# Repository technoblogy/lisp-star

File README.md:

# Lisp Star
A star-shaped pendant that you can program in Lisp.

For more information see: <http://www.technoblogy.com/show?2AMW>.

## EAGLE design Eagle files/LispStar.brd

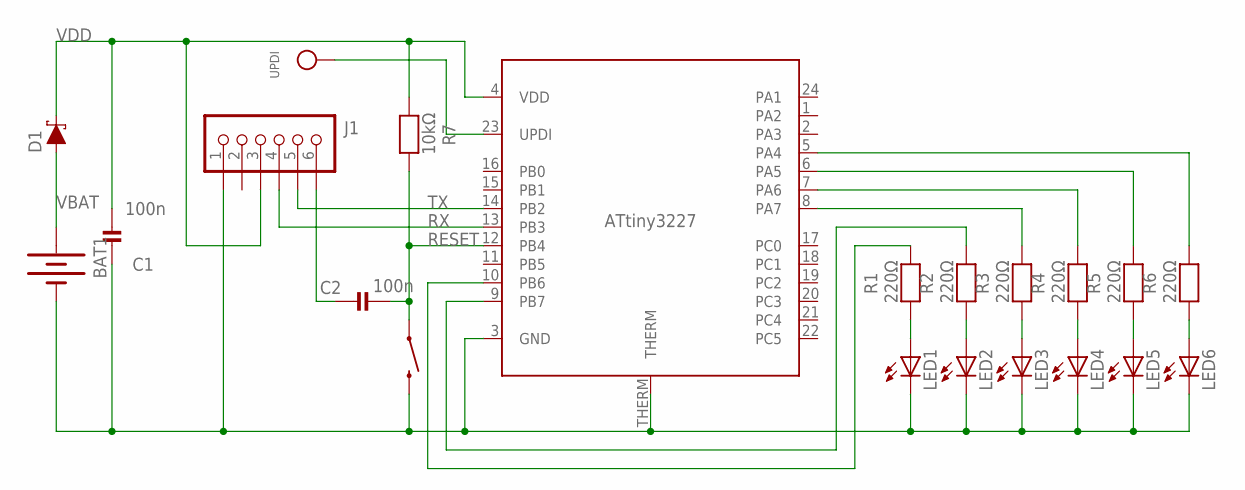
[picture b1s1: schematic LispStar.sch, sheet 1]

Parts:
BAT1: BATTERY12MM; BATTCON_12MM
C1, C2: 100n; _0805MP
D1: 3A/10V/280mV; SOD-323
J1: AVR_SPI_PRG_6LINETESTPOINTS; 2X3_TEST_POINTS
LED1, LED2, LED3, LED4, LED5, LED6: LEDCHIPLED_0805; CHIPLED_0805
R1, R2, R3, R4, R5, R6: 220Ω; _0805MP
R7: 10kΩ; _0805MP
S2: SWITCH-MOMENTARY-2SMD; TACTILE-SWITCH-SMD
U1: ATtiny3227; QFN24_4MM
UPDI: TESTPOINTROUND1MM; TESTPOINT_ROUND_1MM

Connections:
GND: BAT1.GND (-), C1.2, J1.1, LED1.C, LED2.C, LED3.C, LED4.C, LED5.C, LED6.C, S2.3 (2), U1.3 (GND), U1.THERM
unnamed: U1.23 (UPDI), UPDI.P$1
unnamed: LED2.A, R2.1
unnamed: LED1.A, R1.1
unnamed: LED3.A, R3.1
unnamed: C2.1, J1.6
unnamed: LED4.A, R4.1
unnamed: LED5.A, R5.1
unnamed: LED6.A, R6.1
unnamed: R6.2, U1.5 (PA4)
unnamed: R5.2, U1.6 (PA5)
unnamed: R4.2, U1.7 (PA6)
unnamed: R3.2, U1.8 (PA7)
unnamed: R2.2, U1.9 (PB7)
unnamed: R1.2, U1.10 (PB6)
RESET: C2.2, R7.1, S2.1, U1.12 (PB4)
RX: J1.4, U1.13 (PB3)
TX: J1.5, U1.14 (PB2)
VBAT: BAT1.PWR@1 (+), D1.A
VDD: C1.1, D1.C, J1.3, R7.2, U1.4 (VDD)

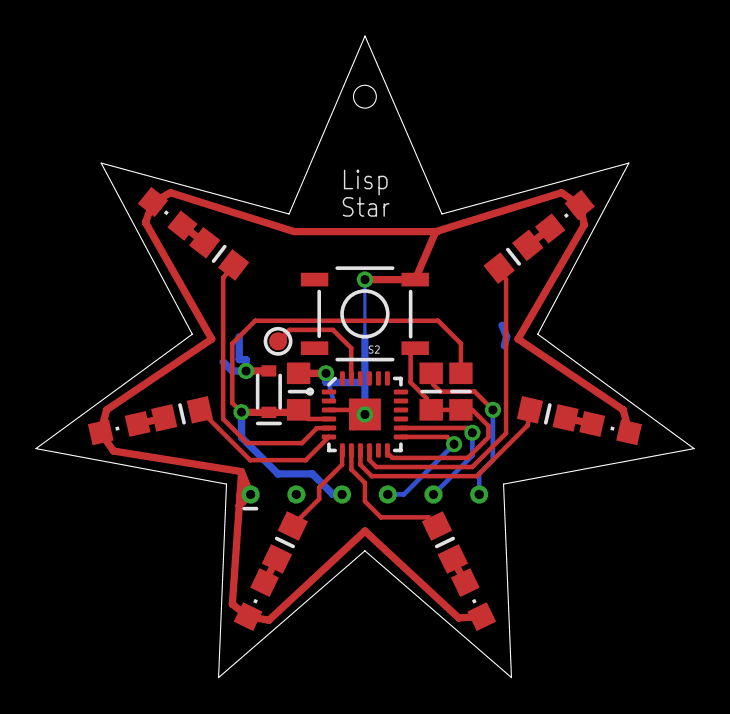
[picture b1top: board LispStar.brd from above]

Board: 2 copper layers, 36.6 x 35.6 mm, 21 parts (1 on the bottom side), 20 nets.

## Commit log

2022-12-08 Version 1 - 8th December 2022

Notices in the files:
parts and their libraries:
SparkFun-Electromechanical: Licensing: Creative Commons ShareAlike 4.0 International - https://creativecommons.org/licenses/by-sa/4.0
microbuilder: This work is placed in the public domain, and may be freely used for commercial and non-commercial work with the following conditions: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
